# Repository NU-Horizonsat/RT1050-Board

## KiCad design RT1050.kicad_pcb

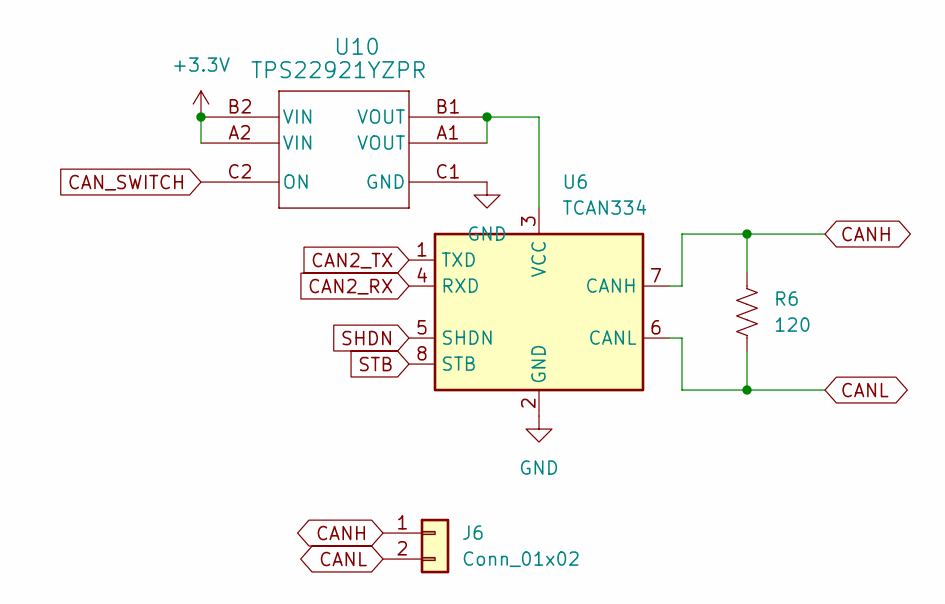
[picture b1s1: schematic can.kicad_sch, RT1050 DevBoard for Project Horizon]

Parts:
J6: Conn_01x02; JST_SH_BM02B-SRSS-TB_1x02-1MP_P1.00mm_Vertical
R6: 120; R_0402_1005Metric
U6: TCAN334; DCN0008A_M
U10: TPS22921YZPR; YZP6

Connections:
+3.3V: U10.A2 (VIN), U10.B2 (VIN); also elsewhere on the board
CAN2_RX: U6.4 (RXD); also elsewhere on the board
CAN2_TX: U6.1 (TXD); also elsewhere on the board
CANH: J6.1, R6.1, U6.7 (CANH)
CANL: J6.2, R6.2, U6.6 (CANL)
CAN_SWITCH: U10.C2 (ON); also elsewhere on the board
GND: U6.2 (GND), U10.C1 (GND); also elsewhere on the board
unnamed: U6.3 (VCC), U10.A1 (VOUT), U10.B1 (VOUT)
SHDN: U6.5 (SHDN); also elsewhere on the board
STB: U6.8 (STB); also elsewhere on the board

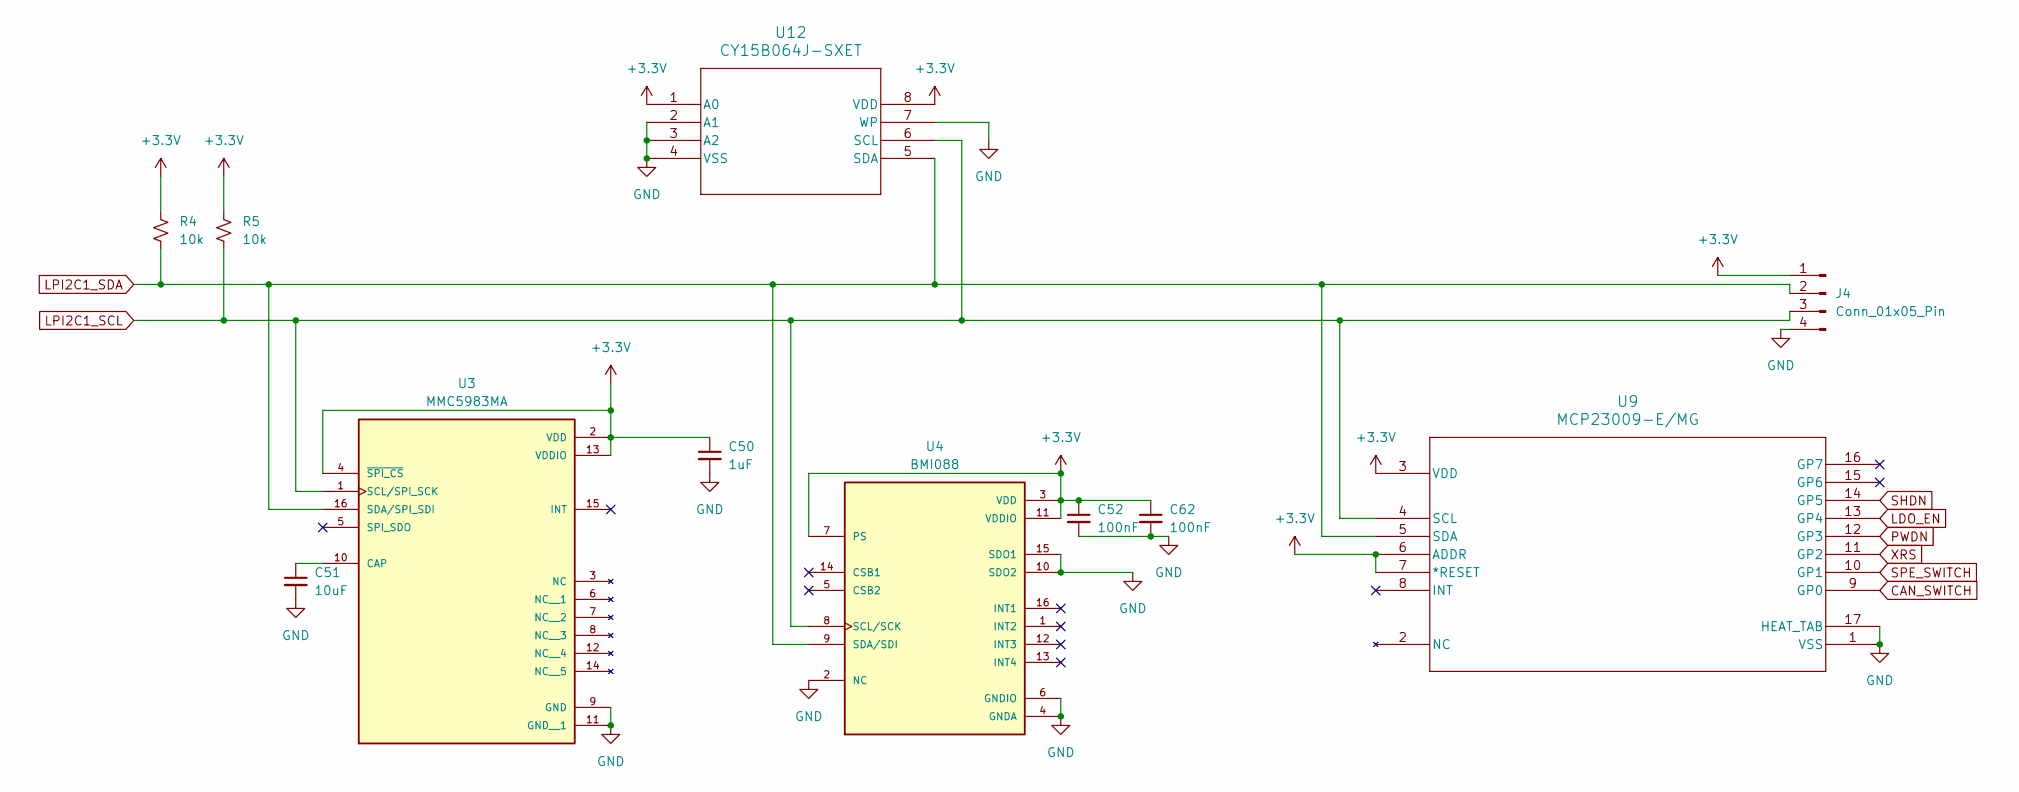
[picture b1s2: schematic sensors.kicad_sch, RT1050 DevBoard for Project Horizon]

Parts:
C50: 1uF; C_0201_0603Metric
C51: 10uF; C_0402_1005Metric
C52, C62: 100nF; C_0201_0603Metric
J4: Conn_01x05_Pin; PinHeader_1x04_P2.00mm_Vertical
R4, R5: 10k; R_0402_1005Metric
U3: MMC5983MA; MMC5983MA_MEM; PARTREV A
U4: BMI088; QFN_BMI085_BOS
U9: MCP23009-E/MG; QFN16_3x3MC_MCH
U12: CY15B064J-SXET; SO8_CY15_CYP

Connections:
+3.3V: C50.1, C52.1, C62.1, J4.1, R4.1, R5.1, U3.2 (VDD), U3.4 (~SPI_CS), U3.13 (VDDIO), U4.3 (VDD), U4.7 (PS), U4.11 (VDDIO), U9.3 (VDD), U9.6 (ADDR), U9.7 (*RESET), U12.1 (A0), U12.8 (VDD); also elsewhere on the board
CAN_SWITCH: U9.9 (GP0); also elsewhere on the board
GND: C50.2, C51.2, C52.2, C62.2, J4.4, U3.9 (GND), U3.11 (GND__1), U4.2 (NC), U4.4 (GNDA), U4.6 (GNDIO), U4.10 (SDO2), U4.15 (SDO1), U9.1 (VSS), U9.17 (HEAT_TAB), U12.2 (A1), U12.3 (A2), U12.4 (VSS), U12.7 (WP); also elsewhere on the board
LDO_EN: U9.13 (GP4); also elsewhere on the board
LPI2C1_SCL: J4.3, R5.2, U3.1 (SCL/SPI_SCK), U4.8 (SCL/SCK), U9.4 (SCL), U12.6 (SCL); also elsewhere on the board
LPI2C1_SDA: J4.2, R4.2, U3.16 (SDA/SPI_SDI), U4.9 (SDA/SDI), U9.5 (SDA), U12.5 (SDA); also elsewhere on the board
unnamed: C51.1, U3.10 (CAP)
PWDN: U9.12 (GP3); also elsewhere on the board
SHDN: U9.14 (GP5); also elsewhere on the board
SPE_SWITCH: U9.10 (GP1); also elsewhere on the board
XRS: U9.11 (GP2); also elsewhere on the board

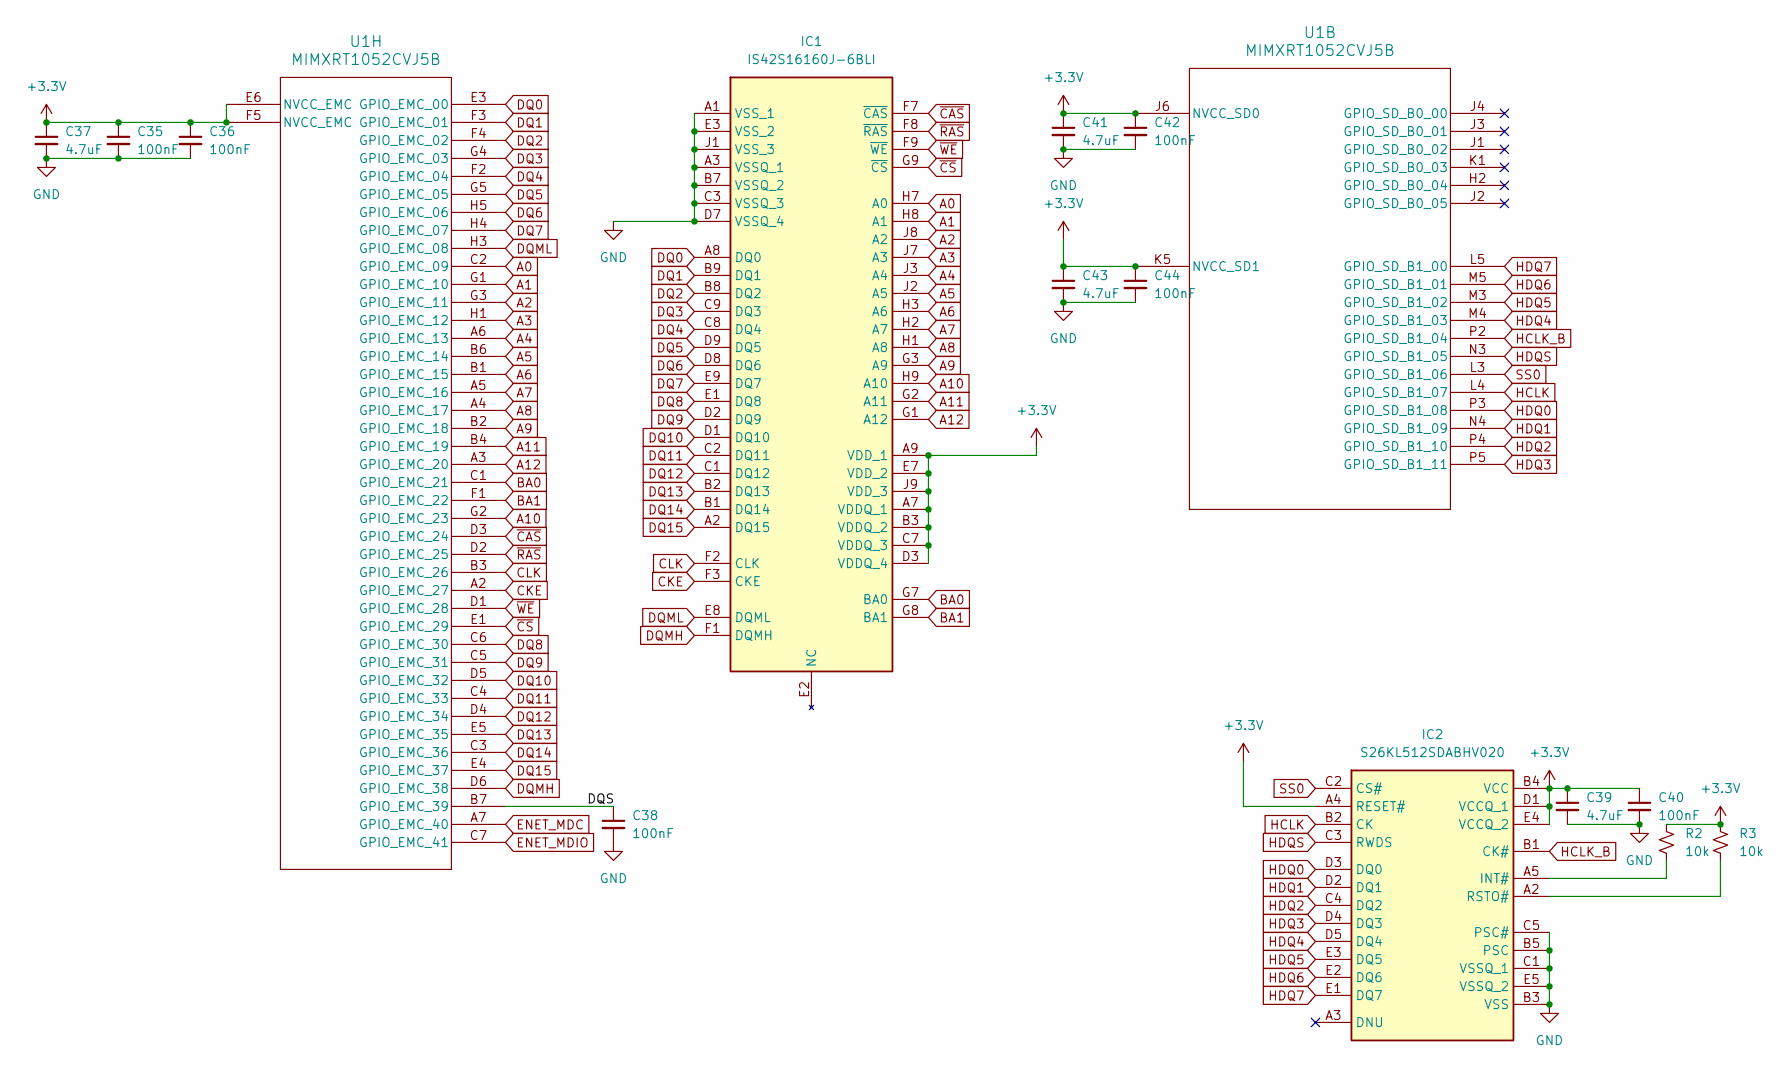
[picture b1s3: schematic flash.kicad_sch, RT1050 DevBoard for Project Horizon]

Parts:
C35, C36, C38, C40, C42, C44: 100nF; C_0201_0603Metric
C37, C39, C41, C43: 4.7uF; C_0201_0603Metric
IC1: IS42S16160J-6BLI; BGA54C80P9X9_800X800X120; Mouser Part Number 870-42S16160J6BLI
IC2: S26KL512SDABHV020; BGA24C100P5X5_600X800X100; Mouser Part Number 727-26KS512SDPBHV020
R2, R3: 10k; R_0402_1005Metric
U1: MIMXRT1052CVJ5B; MAPBGA196_12X12

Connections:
+3.3V: C35.1, C36.1, C37.1, C39.1, C40.1, C41.1, C42.1, C43.1, C44.1, IC1.A7 (VDDQ_1), IC1.A9 (VDD_1), IC1.B3 (VDDQ_2), IC1.C7 (VDDQ_3), IC1.D3 (VDDQ_4), IC1.E7 (VDD_2), IC1.J9 (VDD_3), IC2.A4 (RESET#), IC2.B4 (VCC), IC2.D1 (VCCQ_1), IC2.E4 (VCCQ_2), R2.1, R3.1, U1.E6 (NVCC_EMC), U1.F5 (NVCC_EMC), U1.J6 (NVCC_SD0), U1.K5 (NVCC_SD1); also elsewhere on the board
/Flash & Memory/DQS: C38.1, U1.B7 (GPIO_EMC_39)
A0: IC1.H7 (A0), U1.C2 (GPIO_EMC_09)
A1: IC1.H8 (A1), U1.G1 (GPIO_EMC_10)
A2: IC1.J8 (A2), U1.G3 (GPIO_EMC_11)
A3: IC1.J7 (A3), U1.H1 (GPIO_EMC_12)
A4: IC1.J3 (A4), U1.A6 (GPIO_EMC_13)
A5: IC1.J2 (A5), U1.B6 (GPIO_EMC_14)
A6: IC1.H3 (A6), U1.B1 (GPIO_EMC_15)
A7: IC1.H2 (A7), U1.A5 (GPIO_EMC_16)
A8: IC1.H1 (A8), U1.A4 (GPIO_EMC_17)
A9: IC1.G3 (A9), U1.B2 (GPIO_EMC_18)
A10: IC1.H9 (A10), U1.G2 (GPIO_EMC_23)
A11: IC1.G2 (A11), U1.B4 (GPIO_EMC_19)
A12: IC1.G1 (A12), U1.A3 (GPIO_EMC_20)
BA0: IC1.G7 (BA0), U1.C1 (GPIO_EMC_21)
BA1: IC1.G8 (BA1), U1.F1 (GPIO_EMC_22)
CKE: IC1.F3 (CKE), U1.A2 (GPIO_EMC_27)
CLK: IC1.F2 (CLK), U1.B3 (GPIO_EMC_26)
DQ0: IC1.A8 (DQ0), U1.E3 (GPIO_EMC_00)
DQ1: IC1.B9 (DQ1), U1.F3 (GPIO_EMC_01)
DQ2: IC1.B8 (DQ2), U1.F4 (GPIO_EMC_02)
DQ3: IC1.C9 (DQ3), U1.G4 (GPIO_EMC_03)
DQ4: IC1.C8 (DQ4), U1.F2 (GPIO_EMC_04)
DQ5: IC1.D9 (DQ5), U1.G5 (GPIO_EMC_05)
DQ6: IC1.D8 (DQ6), U1.H5 (GPIO_EMC_06)
DQ7: IC1.E9 (DQ7), U1.H4 (GPIO_EMC_07)
DQ8: IC1.E1 (DQ8), U1.C6 (GPIO_EMC_30)
DQ9: IC1.D2 (DQ9), U1.C5 (GPIO_EMC_31)
DQ10: IC1.D1 (DQ10), U1.D5 (GPIO_EMC_32)
DQ11: IC1.C2 (DQ11), U1.C4 (GPIO_EMC_33)
DQ12: IC1.C1 (DQ12), U1.D4 (GPIO_EMC_34)
DQ13: IC1.B2 (DQ13), U1.E5 (GPIO_EMC_35)
DQ14: IC1.B1 (DQ14), U1.C3 (GPIO_EMC_36)
DQ15: IC1.A2 (DQ15), U1.E4 (GPIO_EMC_37)
DQMH: IC1.F1 (DQMH), U1.D6 (GPIO_EMC_38)
DQML: IC1.E8 (DQML), U1.H3 (GPIO_EMC_08)
ENET_MDC: U1.A7 (GPIO_EMC_40); also elsewhere on the board
ENET_MDIO: U1.C7 (GPIO_EMC_41); also elsewhere on the board
GND: C35.2, C36.2, C37.2, C38.2, C39.2, C40.2, C41.2, C42.2, C43.2, C44.2, IC1.A1 (VSS_1), IC1.A3 (VSSQ_1), IC1.B7 (VSSQ_2), IC1.C3 (VSSQ_3), IC1.D7 (VSSQ_4), IC1.E3 (VSS_2), IC1.J1 (VSS_3), IC2.B3 (VSS), IC2.B5 (PSC), IC2.C1 (VSSQ_1), IC2.C5 (PSC#), IC2.E5 (VSSQ_2); also elsewhere on the board
HCLK: IC2.B2 (CK), U1.L4 (GPIO_SD_B1_07)
HCLK_B: IC2.B1 (CK#), U1.P2 (GPIO_SD_B1_04)
HDQ0: IC2.D3 (DQ0), U1.P3 (GPIO_SD_B1_08)
HDQ1: IC2.D2 (DQ1), U1.N4 (GPIO_SD_B1_09)
HDQ2: IC2.C4 (DQ2), U1.P4 (GPIO_SD_B1_10)
HDQ3: IC2.D4 (DQ3), U1.P5 (GPIO_SD_B1_11)
HDQ4: IC2.D5 (DQ4), U1.M4 (GPIO_SD_B1_03)
HDQ5: IC2.E3 (DQ5), U1.M3 (GPIO_SD_B1_02)
HDQ6: IC2.E2 (DQ6), U1.M5 (GPIO_SD_B1_01)
HDQ7: IC2.E1 (DQ7), U1.L5 (GPIO_SD_B1_00)
HDQS: IC2.C3 (RWDS), U1.N3 (GPIO_SD_B1_05)
unnamed: IC2.A5 (INT#), R2.2
unnamed: IC2.A2 (RSTO#), R3.2
SS0: IC2.C2 (CS#), U1.L3 (GPIO_SD_B1_06)
~CAS: IC1.F7 (~CAS), U1.D3 (GPIO_EMC_24)
~CS: IC1.G9 (~CS), U1.E1 (GPIO_EMC_29)
~RAS: IC1.F8 (~RAS), U1.D2 (GPIO_EMC_25)
~WE: IC1.F9 (~WE), U1.D1 (GPIO_EMC_28)

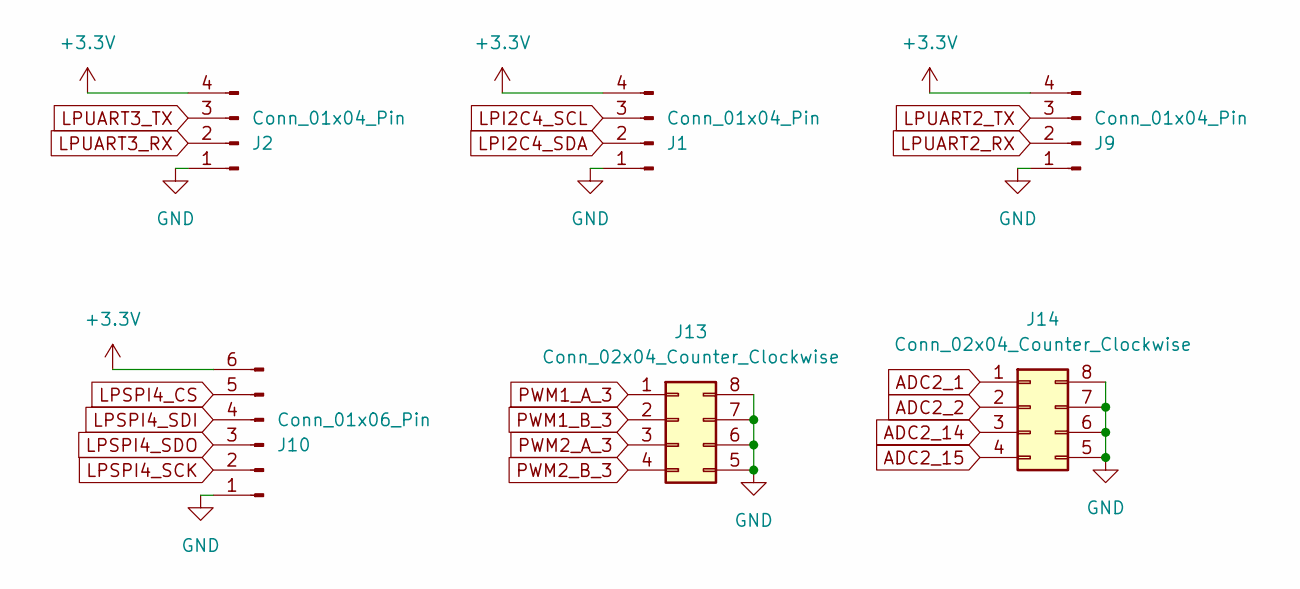
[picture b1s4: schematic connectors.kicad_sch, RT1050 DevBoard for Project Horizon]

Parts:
J1, J2, J9: Conn_01x04_Pin; PinHeader_1x04_P2.00mm_Vertical
J10: Conn_01x06_Pin; PinHeader_1x06_P2.00mm_Vertical
J13, J14: Conn_02x04_Counter_Clockwise; PinHeader_2x04_P2.00mm_Vertical

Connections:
+3.3V: J1.4, J2.4, J9.4, J10.6; also elsewhere on the board
ADC2_1: J14.1; also elsewhere on the board
ADC2_2: J14.2; also elsewhere on the board
ADC2_14: J14.3; also elsewhere on the board
ADC2_15: J14.4; also elsewhere on the board
GND: J1.1, J2.1, J9.1, J10.1, J13.5, J13.6, J13.7, J13.8, J14.5, J14.6, J14.7, J14.8; also elsewhere on the board
LPI2C4_SCL: J1.3; also elsewhere on the board
LPI2C4_SDA: J1.2; also elsewhere on the board
LPSPI4_CS: J10.5; also elsewhere on the board
LPSPI4_SCK: J10.2; also elsewhere on the board
LPSPI4_SDI: J10.4; also elsewhere on the board
LPSPI4_SDO: J10.3; also elsewhere on the board
LPUART2_RX: J9.2; also elsewhere on the board
LPUART2_TX: J9.3; also elsewhere on the board
LPUART3_RX: J2.2; also elsewhere on the board
LPUART3_TX: J2.3; also elsewhere on the board
PWM1_A_3: J13.1; also elsewhere on the board
PWM1_B_3: J13.2; also elsewhere on the board
PWM2_A_3: J13.3; also elsewhere on the board
PWM2_B_3: J13.4; also elsewhere on the board

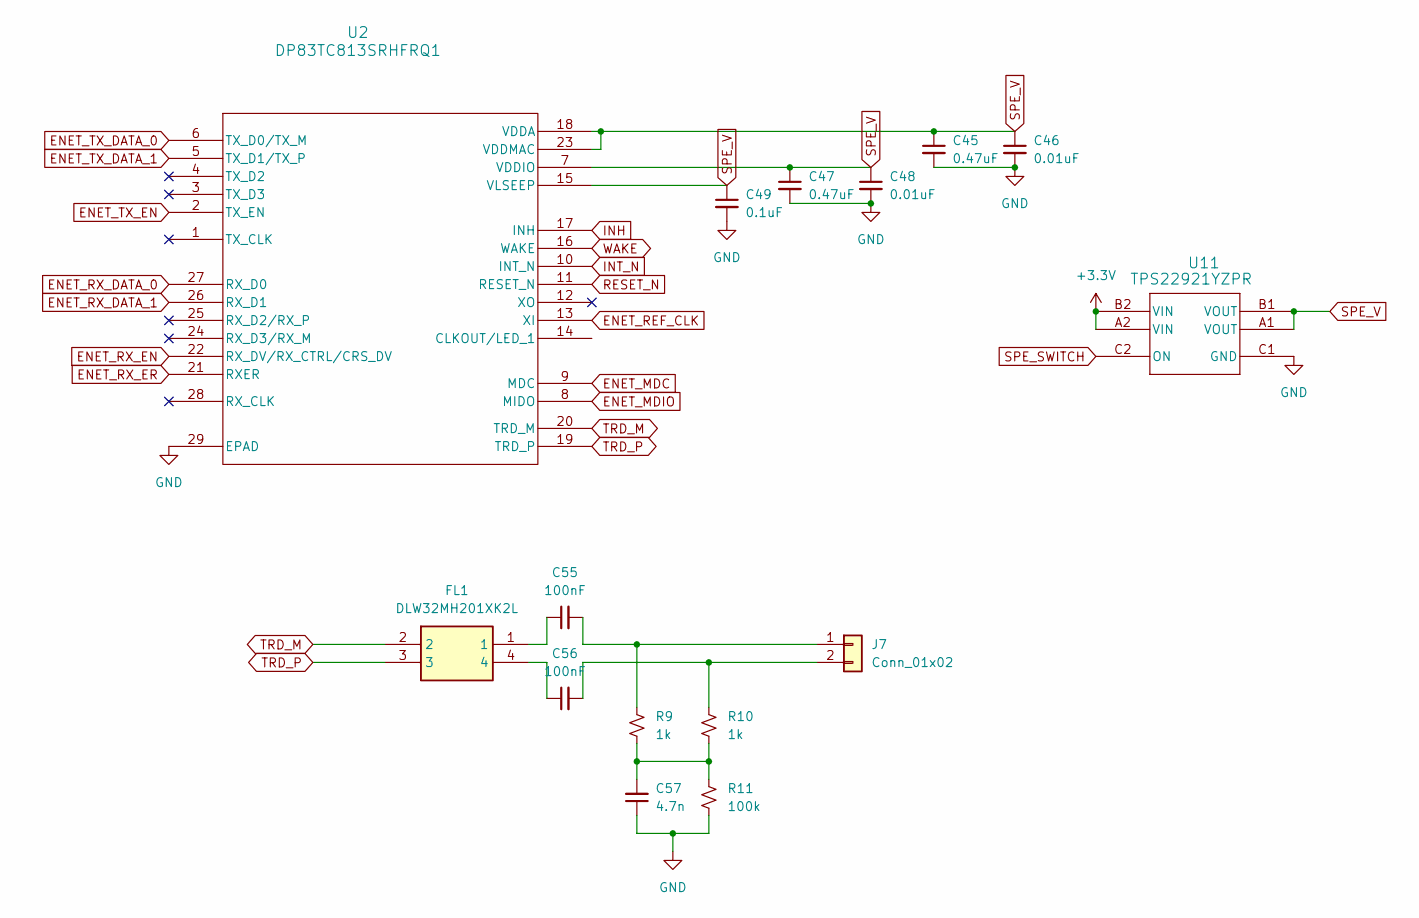
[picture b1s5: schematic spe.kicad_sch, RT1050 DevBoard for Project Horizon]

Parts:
C45, C47: 0.47uF; C_0201_0603Metric
C46, C48: 0.01uF; C_0201_0603Metric
C49: 0.1uF; C_0201_0603Metric
C55, C56: 100nF; C_0201_0603Metric
C57: 4.7n; C_0201_0603Metric
FL1: DLW32MH201XK2L; DLW32MH101XK2L; Mouser Part Number 81-DLW32MH201XK2L
J7: Conn_01x02; JST_PH_B2B-PH-K_1x02_P2.00mm_Vertical
R9, R10: 1k; R_0402_1005Metric
R11: 100k; R_0402_1005Metric
U2: DP83TC813SRHFRQ1; VQFN28_RHF_TEX
U11: TPS22921YZPR; YZP6

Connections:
+3.3V: U11.A2 (VIN), U11.B2 (VIN); also elsewhere on the board
ENET_MDC: U2.9 (MDC); also elsewhere on the board
ENET_MDIO: U2.8 (MIDO); also elsewhere on the board
ENET_REF_CLK: U2.13 (XI); also elsewhere on the board
ENET_RX_DATA_0: U2.27 (RX_D0); also elsewhere on the board
ENET_RX_DATA_1: U2.26 (RX_D1); also elsewhere on the board
ENET_RX_EN: U2.22 (RX_DV/RX_CTRL/CRS_DV); also elsewhere on the board
ENET_RX_ER: U2.21 (RXER); also elsewhere on the board
ENET_TX_DATA_0: U2.6 (TX_D0/TX_M); also elsewhere on the board
ENET_TX_DATA_1: U2.5 (TX_D1/TX_P); also elsewhere on the board
ENET_TX_EN: U2.2 (TX_EN); also elsewhere on the board
GND: C45.2, C46.2, C47.2, C48.2, C49.2, C57.1, R11.2, U2.29 (EPAD), U11.C1 (GND); also elsewhere on the board
INH: U2.17 (INH); also elsewhere on the board
INT_N: U2.10 (INT_N); also elsewhere on the board
unnamed: C55.1, FL1.1
unnamed: C56.1, FL1.4
unnamed: C57.2, R9.2, R10.2, R11.1
unnamed: C55.2, J7.1, R9.1
unnamed: C56.2, J7.2, R10.1
RESET_N: U2.11 (RESET_N); also elsewhere on the board
SPE_SWITCH: U11.C2 (ON); also elsewhere on the board
SPE_V: C45.1, C46.1, C47.1, C48.1, C49.1, U2.7 (VDDIO), U2.15 (VLSEEP), U2.18 (VDDA), U2.23 (VDDMAC), U11.A1 (VOUT), U11.B1 (VOUT)
TRD_M: FL1.2, U2.20 (TRD_M)
TRD_P: FL1.3, U2.19 (TRD_P)
WAKE: U2.16 (WAKE); also elsewhere on the board

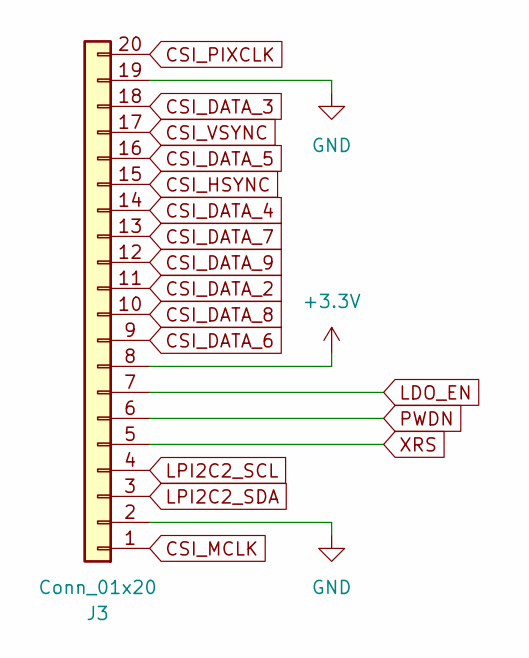
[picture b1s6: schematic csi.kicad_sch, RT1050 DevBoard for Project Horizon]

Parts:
J3: Conn_01x20; Molex_200528-0200_1x20-1MP_P1.00mm_Horizontal

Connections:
+3.3V: J3.8; also elsewhere on the board
CSI_DATA_2: J3.11; also elsewhere on the board
CSI_DATA_3: J3.18; also elsewhere on the board
CSI_DATA_4: J3.14; also elsewhere on the board
CSI_DATA_5: J3.16; also elsewhere on the board
CSI_DATA_6: J3.9; also elsewhere on the board
CSI_DATA_7: J3.13; also elsewhere on the board
CSI_DATA_8: J3.10; also elsewhere on the board
CSI_DATA_9: J3.12; also elsewhere on the board
CSI_HSYNC: J3.15; also elsewhere on the board
CSI_MCLK: J3.1; also elsewhere on the board
CSI_PIXCLK: J3.20; also elsewhere on the board
CSI_VSYNC: J3.17; also elsewhere on the board
GND: J3.2, J3.19; also elsewhere on the board
LDO_EN: J3.7; also elsewhere on the board
LPI2C2_SCL: J3.4; also elsewhere on the board
LPI2C2_SDA: J3.3; also elsewhere on the board
PWDN: J3.6; also elsewhere on the board
XRS: J3.5; also elsewhere on the board

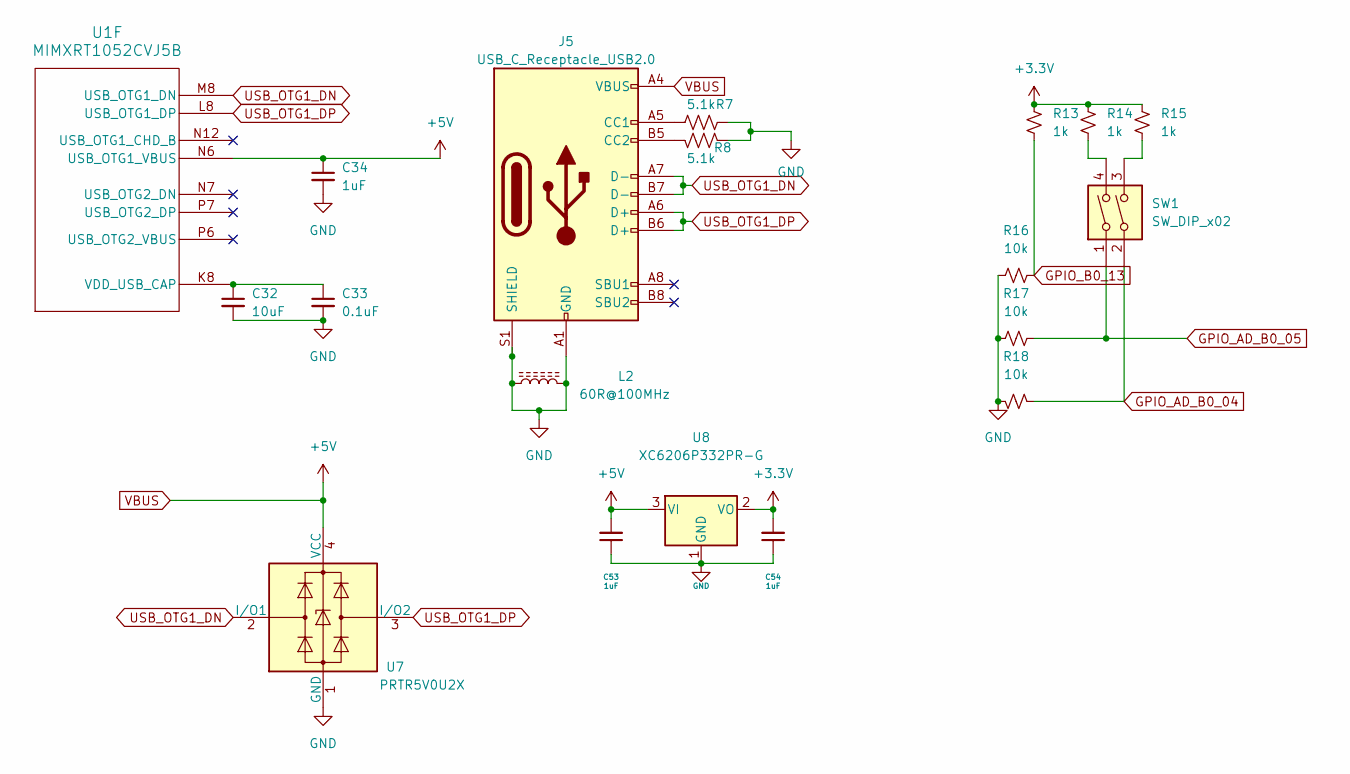
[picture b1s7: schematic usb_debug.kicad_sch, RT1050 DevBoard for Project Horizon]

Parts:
C32: 10uF; C_0402_1005Metric
C33: 0.1uF; C_0201_0603Metric
C34: 1uF; C_0201_0603Metric
C53, C54: 1uF; C_0201_0603Metric; LCSC C52923
J5: USB_C_Receptacle_USB2.0; USB_C_Receptacle_HRO_TYPE-C-31-M-12; JlcRotOffset 180
L2: 60R@100MHz; L_1206_3216Metric; Manufacturer Part No MLB3216-600P4A(f); LCSC C33600
R7, R8: 5.1k; R_0402_1005Metric
R13, R14, R15: 1k; R_0402_1005Metric
R16, R17, R18: 10k; R_0402_1005Metric
SW1: SW_DIP_x02; SW_DIP_SPSTx02_Slide_6.7x6.64mm_W6.73mm_P2.54mm_LowProfile_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
U1: MIMXRT1052CVJ5B; MAPBGA196_12X12
U7: PRTR5V0U2X; SOT-143; LCSC C2827688
U8: XC6206P332PR-G; SOT-23; LCSC C5446

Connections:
+3.3V: C54.2, R13.1, R14.1, R15.1, U8.2 (VO); also elsewhere on the board
CSI_DATA_8: R17.2, SW1.1; also elsewhere on the board
GND: C32.2, C33.2, C34.2, C53.1, C54.1, J5.A1 (GND), J5.A12 (GND), J5.B1 (GND), J5.B12 (GND), J5.S1 (SHIELD), L2.1, L2.2, R7.1, R8.1, R16.1, R17.1, R18.2, U7.1 (GND), U8.1 (GND); also elsewhere on the board
GPIO_AD_B0_04: R18.1, SW1.2; also elsewhere on the board
GPIO_B0_13: R13.2, R16.2; also elsewhere on the board
unnamed: J5.A5 (CC1), R7.2
unnamed: J5.B5 (CC2), R8.2
unnamed: R14.2, SW1.4
unnamed: R15.2, SW1.3
unnamed: C32.1, C33.1, U1.K8 (VDD_USB_CAP)
USB_OTG1_DN: J5.A7 (D-), J5.B7 (D-), U1.M8 (USB_OTG1_DN), U7.2 (I/O1)
USB_OTG1_DP: J5.A6 (D+), J5.B6 (D+), U1.L8 (USB_OTG1_DP), U7.3 (I/O2)
VBUS: C34.1, C53.2, J5.A4 (VBUS), J5.A9 (VBUS), J5.B4 (VBUS), J5.B9 (VBUS), U1.N6 (USB_OTG1_VBUS), U7.4 (VCC), U8.3 (VI)

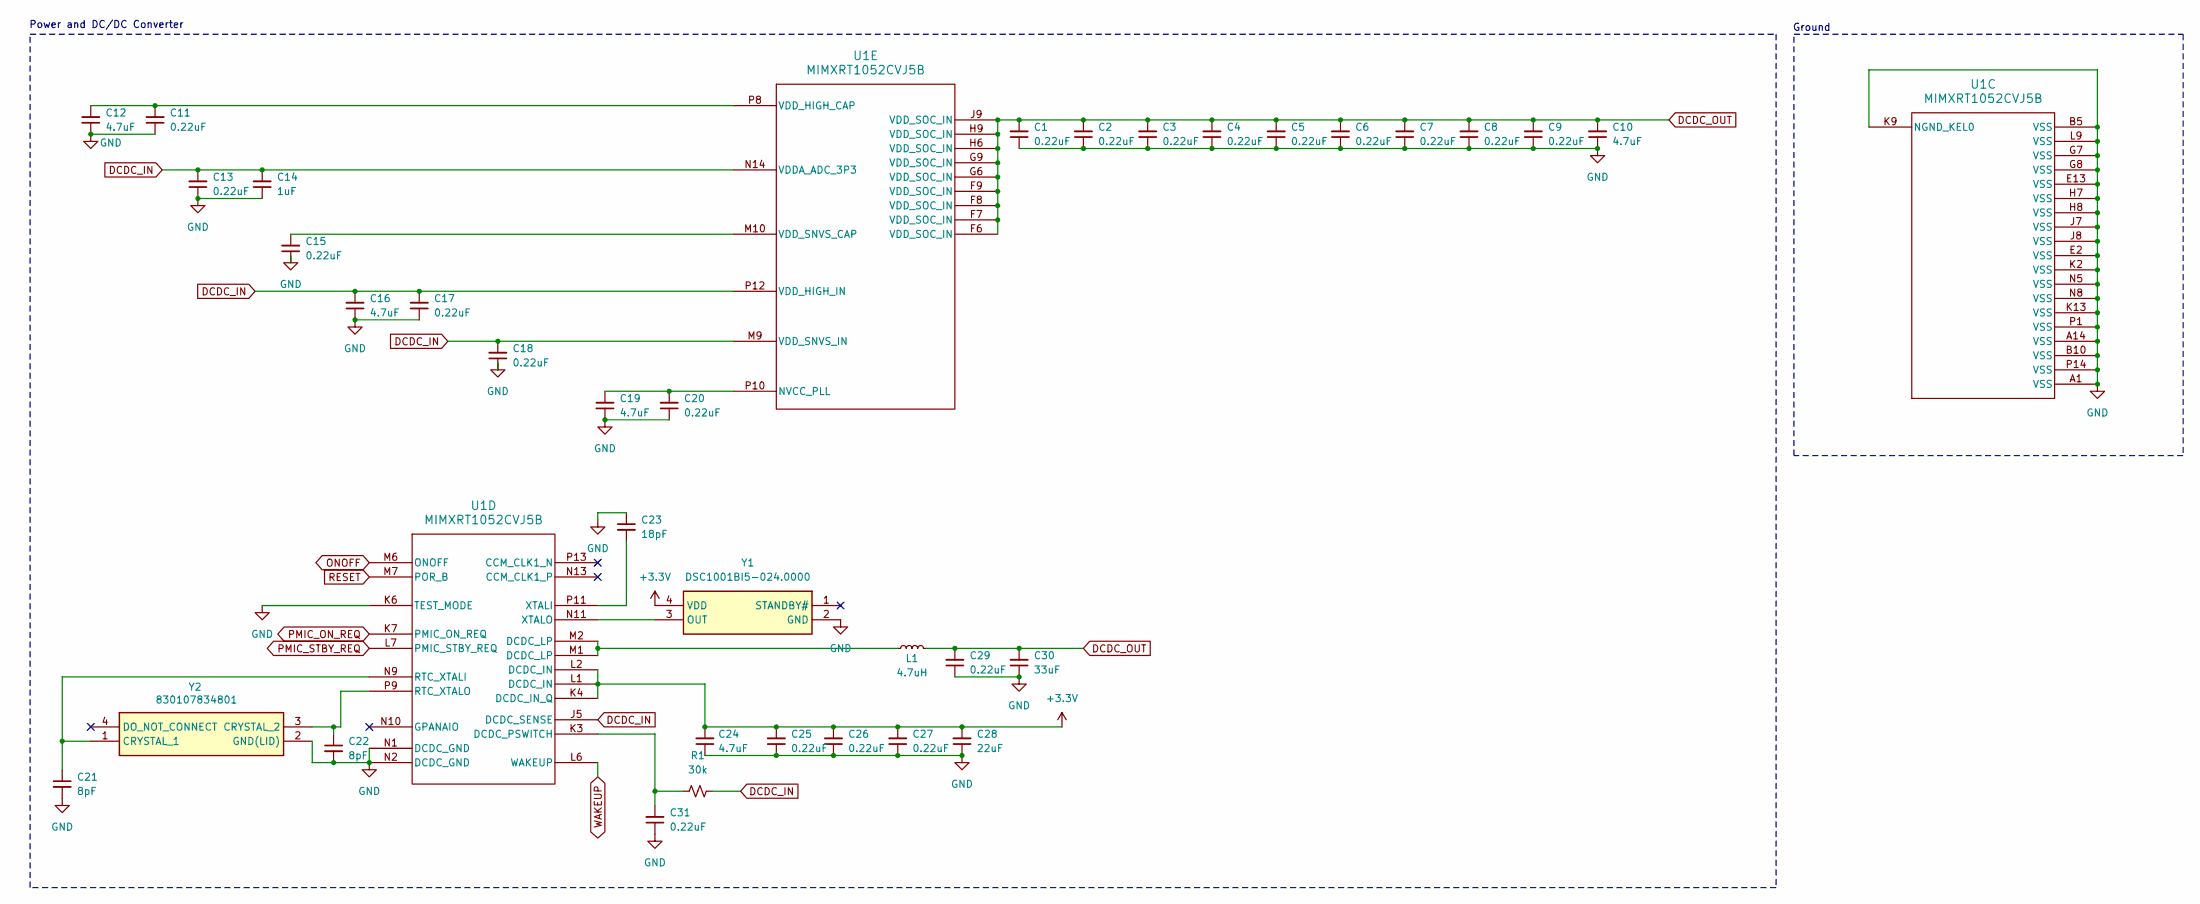
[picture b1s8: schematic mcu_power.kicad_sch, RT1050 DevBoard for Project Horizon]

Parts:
C1, C2, C3, C4, C5, C6, C7, C8, C9, C11, C13, C15, C17, C18, C20, C25, C26, C27, C29, C31: 0.22uF; C_0201_0603Metric
C10, C12, C16, C19, C24: 4.7uF; C_0201_0603Metric
C14: 1uF; C_0201_0603Metric
C21, C22: 8pF; C_0201_0603Metric
C23: 18pF; C_0201_0603Metric
C28: 22uF; C_0603_1608Metric
C30: 33uF; C_0805_2012Metric
L1: 4.7uH; L_0603_1608Metric
R1: 30k; R_0402_1005Metric
U1: MIMXRT1052CVJ5B; MAPBGA196_12X12
Y1: DSC1001BI5-024.0000; CDFN4_5X3P2_MCH; Mouser Part Number 579-001BI50240000
Y2: 830107834801; WE-XTAL_IQXC-146; Mouser Part Number 710-830107834801

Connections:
+3.3V: C24.2, C25.2, C26.2, C27.2, C28.2, U1.K4 (DCDC_IN_Q), U1.L1 (DCDC_IN), U1.L2 (DCDC_IN), Y1.4 (VDD); also elsewhere on the board
DCDC_IN: C13.2, C14.2, C16.2, C17.2, C18.2, R1.2, U1.J5 (DCDC_SENSE), U1.M9 (VDD_SNVS_IN), U1.N14 (VDDA_ADC_3P3), U1.P12 (VDD_HIGH_IN)
DCDC_OUT: C1.2, C2.2, C3.2, C4.2, C5.2, C6.2, C7.2, C8.2, C9.2, C10.2, C29.2, C30.2, L1.1, U1.F6 (VDD_SOC_IN), U1.F7 (VDD_SOC_IN), U1.F8 (VDD_SOC_IN), U1.F9 (VDD_SOC_IN), U1.G6 (VDD_SOC_IN), U1.G9 (VDD_SOC_IN), U1.H6 (VDD_SOC_IN), U1.H9 (VDD_SOC_IN), U1.J9 (VDD_SOC_IN)
GND: C1.1, C2.1, C3.1, C4.1, C5.1, C6.1, C7.1, C8.1, C9.1, C10.1, C11.1, C12.1, C13.1, C14.1, C15.1, C16.1, C17.1, C18.1, C19.1, C20.1, C21.2, C22.2, C23.1, C24.1, C25.1, C26.1, C27.1, C28.1, C29.1, C30.1, C31.1, U1.A1 (VSS), U1.A14 (VSS), U1.B5 (VSS), U1.B10 (VSS), U1.E2 (VSS), U1.E13 (VSS), U1.G7 (VSS), U1.G8 (VSS), U1.H7 (VSS), U1.H8 (VSS), U1.J7 (VSS), U1.J8 (VSS), U1.K2 (VSS), U1.K6 (TEST_MODE), U1.K9 (NGND_KEL0), U1.K13 (VSS), U1.L9 (VSS), U1.N1 (DCDC_GND), U1.N2 (DCDC_GND), U1.N5 (VSS), U1.N8 (VSS), U1.P1 (VSS), U1.P14 (VSS), Y1.2 (GND), Y2.2 (GND(LID)); also elsewhere on the board
unnamed: L1.2, U1.M1 (DCDC_LP), U1.M2 (DCDC_LP)
unnamed: C31.2, R1.1, U1.K3 (DCDC_PSWITCH)
unnamed: C21.1, U1.N9 (RTC_XTALI), Y2.1 (CRYSTAL_1)
unnamed: C22.1, U1.P9 (RTC_XTALO), Y2.3 (CRYSTAL_2)
unnamed: C23.2, U1.P11 (XTALI)
unnamed: U1.N11 (XTALO), Y1.3 (OUT)
unnamed: C19.2, C20.2, U1.P10 (NVCC_PLL)
unnamed: C11.2, C12.2, U1.P8 (VDD_HIGH_CAP)
unnamed: C15.2, U1.M10 (VDD_SNVS_CAP)
ONOFF: U1.M6 (ONOFF)
PMIC_ON_REQ: U1.K7 (PMIC_ON_REQ)
PMIC_STBY_REQ: U1.L7 (PMIC_STBY_REQ)
RESET: U1.M7 (POR_B)
WAKEUP: U1.L6 (WAKEUP)

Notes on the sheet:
Power and DC/DC Converter
Ground

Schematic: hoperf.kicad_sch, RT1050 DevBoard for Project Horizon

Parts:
J8: Conn_Coaxial_Small; SMA_Amphenol_132134_Vertical
R12: 10k; R_0402_1005Metric
U5: RFM98W-433S2; HOPERF_RFM95W_SMD

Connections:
+3.3V: R12.1, U5.13 (3.3V); also elsewhere on the board
DIO0: U5.14 (DIO0); also elsewhere on the board
DIO4: U5.12 (DIO4); also elsewhere on the board
GND: J8.2 (Ext), U5.1 (GND), U5.8 (GND), U5.10 (GND); also elsewhere on the board
HOPERF_RST: U5.6 (RESET); also elsewhere on the board
LPSPI3_CS: R12.2, U5.5 (NSS); also elsewhere on the board
LPSPI3_SCK: U5.4 (SCK); also elsewhere on the board
LPSPI3_SDI: U5.3 (MOSI); also elsewhere on the board
LPSPI3_SDO: U5.2 (MISO); also elsewhere on the board
unnamed: J8.1 (In), U5.9 (ANT)

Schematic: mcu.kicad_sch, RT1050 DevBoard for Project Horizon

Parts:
C58: 4.7uF; C_0201_0603Metric
C59, C60, C61: 100nF; C_0201_0603Metric
U1: MIMXRT1052CVJ5B; MAPBGA196_12X12

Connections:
+3.3V: C58.1, C59.1, C60.1, C61.1, U1.E9 (NVCC_GPIO), U1.F10 (NVCC_GPIO), U1.J10 (NVCC_GPIO); also elsewhere on the board
ADC2_1: U1.H12 (GPIO_AD_B1_12); also elsewhere on the board
ADC2_2: U1.H11 (GPIO_AD_B1_13); also elsewhere on the board
ADC2_14: U1.M13 (GPIO_AD_B1_09); also elsewhere on the board
ADC2_15: U1.L13 (GPIO_AD_B1_10); also elsewhere on the board
CAN2_RX: U1.L10 (GPIO_AD_B0_15); also elsewhere on the board
CAN2_TX: U1.H14 (GPIO_AD_B0_14); also elsewhere on the board
CSI_DATA_2: U1.J14 (GPIO_AD_B1_15); also elsewhere on the board
CSI_DATA_3: U1.G13 (GPIO_AD_B0_10); also elsewhere on the board
CSI_DATA_4: U1.F14 (GPIO_AD_B0_09); also elsewhere on the board
CSI_DATA_5: U1.F13 (GPIO_AD_B0_08); also elsewhere on the board
CSI_DATA_6: U1.J13 (GPIO_AD_B1_11); also elsewhere on the board
CSI_DATA_7: U1.E14 (GPIO_AD_B0_06); also elsewhere on the board
CSI_DATA_8: U1.G14 (GPIO_AD_B0_05); also elsewhere on the board
CSI_DATA_9: U1.H13 (GPIO_AD_B1_08); also elsewhere on the board
CSI_HSYNC: U1.K10 (GPIO_AD_B1_07); also elsewhere on the board
CSI_MCLK: U1.K12 (GPIO_AD_B1_05); also elsewhere on the board
CSI_PIXCLK: U1.L12 (GPIO_AD_B1_04); also elsewhere on the board
CSI_VSYNC: U1.J12 (GPIO_AD_B1_06); also elsewhere on the board
DIO0: U1.A9 (GPIO_B0_07); also elsewhere on the board
DIO4: U1.A8 (GPIO_B0_06); also elsewhere on the board
ENET_REF_CLK: U1.B13 (GPIO_B1_10); also elsewhere on the board
ENET_RX_DATA_0: U1.E12 (GPIO_B1_04); also elsewhere on the board
ENET_RX_DATA_1: U1.D12 (GPIO_B1_05); also elsewhere on the board
ENET_RX_EN: U1.C12 (GPIO_B1_06); also elsewhere on the board
ENET_RX_ER: U1.C13 (GPIO_B1_11); also elsewhere on the board
ENET_TX_DATA_0: U1.B12 (GPIO_B1_07); also elsewhere on the board
ENET_TX_DATA_1: U1.A12 (GPIO_B1_08); also elsewhere on the board
ENET_TX_EN: U1.A13 (GPIO_B1_09); also elsewhere on the board
ENET_TX_ER: U1.F12 (GPIO_AD_B0_07)
GND: C58.2, C59.2, C60.2, C61.2; also elsewhere on the board
GPIO_AD_B0_04: U1.F11 (GPIO_AD_B0_04); also elsewhere on the board
GPIO_B0_13: U1.D10 (GPIO_B0_13); also elsewhere on the board
HOPERF_RST: U1.G11 (GPIO_AD_B0_03); also elsewhere on the board
INH: U1.D13 (GPIO_B1_12); also elsewhere on the board
INT_N: U1.C14 (GPIO_B1_14); also elsewhere on the board
LPI2C1_SCL: U1.J11 (GPIO_AD_B1_00); also elsewhere on the board
LPI2C1_SDA: U1.K11 (GPIO_AD_B1_01); also elsewhere on the board
LPI2C2_SCL: U1.C8 (GPIO_B0_04); also elsewhere on the board
LPI2C2_SDA: U1.B8 (GPIO_B0_05); also elsewhere on the board
LPI2C4_SCL: U1.K14 (GPIO_AD_B0_12); also elsewhere on the board
LPI2C4_SDA: U1.L14 (GPIO_AD_B0_13); also elsewhere on the board
LPSPI3_CS: U1.H10 (GPIO_AD_B0_01); also elsewhere on the board
LPSPI3_SCK: U1.M14 (GPIO_AD_B0_00); also elsewhere on the board
LPSPI3_SDI: U1.M11 (GPIO_AD_B0_02); also elsewhere on the board
LPSPI3_SDO: U1.G12 (GPIO_AD_B1_14); also elsewhere on the board
LPSPI4_CS: U1.D7 (GPIO_B0_00); also elsewhere on the board
LPSPI4_SCK: U1.D8 (GPIO_B0_03); also elsewhere on the board
LPSPI4_SDI: U1.E7 (GPIO_B0_01); also elsewhere on the board
LPSPI4_SDO: U1.E8 (GPIO_B0_02); also elsewhere on the board
LPUART2_RX: U1.M12 (GPIO_AD_B1_03); also elsewhere on the board
LPUART2_TX: U1.L11 (GPIO_AD_B1_02); also elsewhere on the board
LPUART3_RX: U1.C9 (GPIO_B0_09); also elsewhere on the board
LPUART3_TX: U1.B9 (GPIO_B0_08); also elsewhere on the board
PWM1_A_3: U1.A11 (GPIO_B1_00); also elsewhere on the board
PWM1_B_3: U1.B11 (GPIO_B1_01); also elsewhere on the board
PWM2_A_3: U1.C11 (GPIO_B1_02); also elsewhere on the board
PWM2_B_3: U1.D11 (GPIO_B1_03); also elsewhere on the board
RESET_N: U1.B14 (GPIO_B1_15); also elsewhere on the board
STB: U1.A10 (GPIO_B0_11); also elsewhere on the board
WAKE: U1.D14 (GPIO_B1_13); also elsewhere on the board
